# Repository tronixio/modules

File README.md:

# Modules

## GPIO Modules.

- [Breadboard.](https://github.com/tronixio/modules/blob/main/gpio/hc595.md)
- [TODO - 74HC595 - LED & Header.](https://github.com/tronixio/modules/blob/main/gpio/hc595.md)
- [TODO - 74HC4053 - Header.](https://github.com/tronixio/modules/blob/main/gpio/hc4053.md)
- [TODO - DG509B - Header.](https://github.com/tronixio/modules/blob/main/gpio/dg509b.md)
- [TODO - LCD 4x20 Characters.](https://github.com/tronixio/modules/blob/main/gpio/lcd420.md)

## UART Modules.

- [TODO.](https://tronix.io)

## I2C Modules.

- [TODO.](https://tronix.io)

## SPI Modules.

- [TODO.](https://tronix.io)

## Notes.

- DRAFT : Prototype OK, last check schematic, PCB & code can be modify.
- TODO : Work in progress, prototype was not good, hardware, PCB and code can be rework.

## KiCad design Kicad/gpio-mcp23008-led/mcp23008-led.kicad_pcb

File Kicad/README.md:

# Modules.

- [Modules.](https://github.com/tronixio/modules)

## Notes.

- TODO : Work in progress, prototype was not good, hardware, PCB and code can be rework.
- DRAFT : Prototype OK, last check schematic, PCB & code can be modify.

## DISCLAIMER.

THIS CODE IS PROVIDED WITHOUT ANY WARRANTY OR GUARANTEES.
USERS MAY USE THIS CODE FOR DEVELOPMENT AND EXAMPLE PURPOSES ONLY.
AUTHORS ARE NOT RESPONSIBLE FOR ANY ERRORS, OMISSIONS, OR DAMAGES THAT COULD
RESULT FROM USING THIS FIRMWARE IN WHOLE OR IN PART.

---

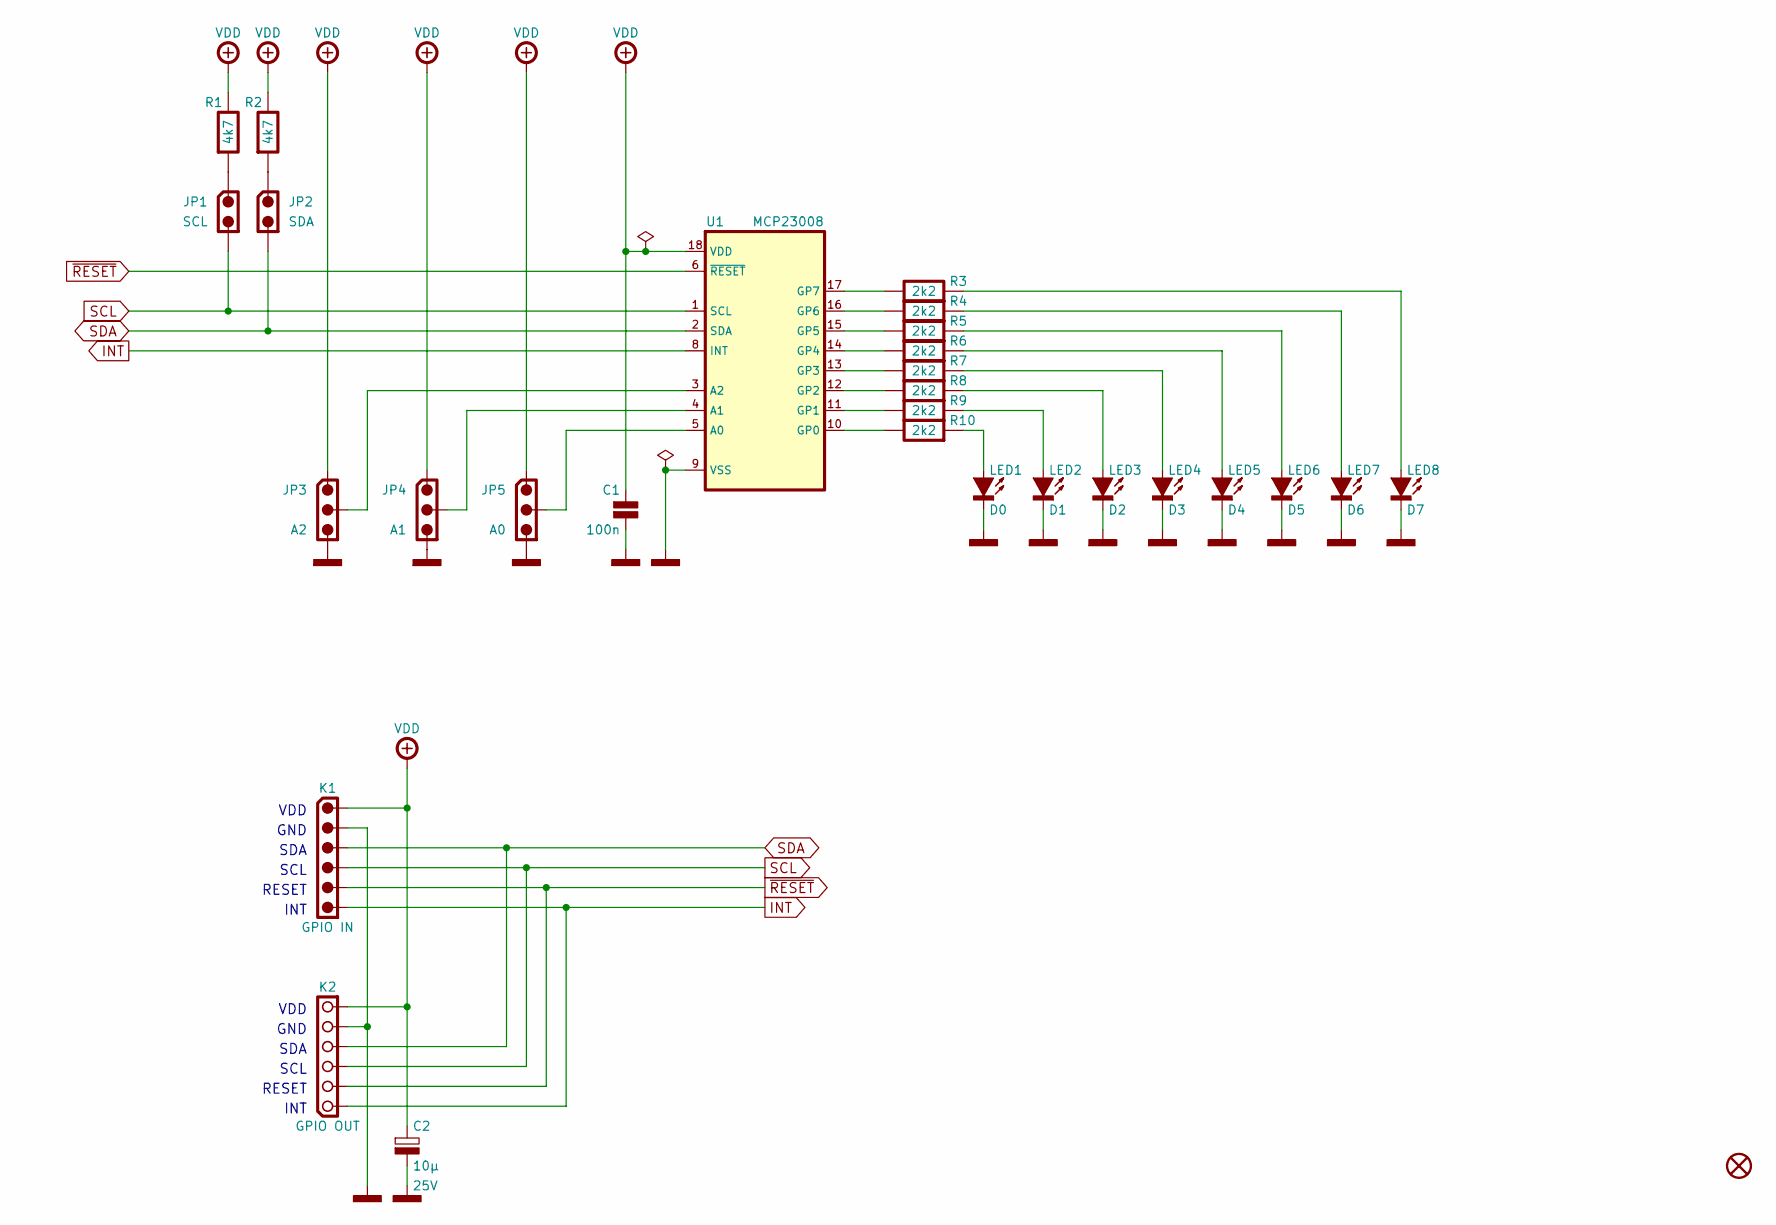
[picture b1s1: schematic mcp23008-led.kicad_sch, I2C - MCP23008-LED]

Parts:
C1: 100n; CAPACITOR-SMD-1206; Voltage 50V; Tolerance 5%; Mouser 80-C1206C104J5R
C2: 10µ; CAPACITOR-SMD-CASE-B; Voltage 25V; Tolerance 10%; Mouser 74-293D106X9025B2TE3
JP1: SCL; HARWIN-M22-25102xx; Mouser 855-M22-25102
JP2: SDA; HARWIN-M22-25102xx; Mouser 855-M22-25102
JP3: A2; HARWIN-M22-25103xx; Mouser 855-M22-25103
JP4: A1; HARWIN-M22-25103xx; Mouser 855-M22-25103
JP5: A0; HARWIN-M22-25103xx; Mouser 855-M22-25103
K1: GPIO IN; HARWIN-M20-975064x; Mouser 855-M20-975064
K2: GPIO OUT; SAMTEC-SSW-106-02-T-S-RA; Mouser 200-SSW10603TSRA
LED1: D0; LED-SMD-1206; Mouser 604-APT3216LSECKJ3RV
LED2: D1; LED-SMD-1206; Mouser 604-APT3216LSECKJ3RV
LED3: D2; LED-SMD-1206; Mouser 604-APT3216LSECKJ3RV
LED4: D3; LED-SMD-1206; Mouser 604-APT3216LSECKJ3RV
LED5: D4; LED-SMD-1206; Mouser 604-APT3216LSECKJ3RV
LED6: D5; LED-SMD-1206; Mouser 604-APT3216LSECKJ3RV
LED7: D6; LED-SMD-1206; Mouser 604-APT3216LSECKJ3RV
LED8: D7; LED-SMD-1206; Mouser 604-APT3216LSECKJ3RV
R1, R2: 4k7; RESISTOR-SMD-0805; Tolerance 5%; Mouser 660-RK73B2ATTDD472J
R3, R4, R5, R6, R7, R8, R9, R10: 2k2; RESISTOR-SMD-1206; Tolerance 5%; Mouser 660-RK73B2BTTDD222J
U1: MCP23008; SOIC-18W; Mouser 579-MCP23008-E/SO
U2: 3M-SJ5376; Mouser 517-SJ5376

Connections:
+VDD: C1.1, C2.1, JP3.1, JP4.1, JP5.1, K1.1, K2.6, R1.1, R2.1, U1.18 (VDD)
GND: C1.2, C2.2, JP3.3, JP4.3, JP5.3, K1.2, K2.5, LED1.1 (C), LED2.1 (C), LED3.1 (C), LED4.1 (C), LED5.1 (C), LED6.1 (C), LED7.1 (C), LED8.1 (C), U1.9 (VSS)
INT: K1.6, K2.1, U1.8 (INT)
unnamed: JP1.1, R1.2
unnamed: JP2.1, R2.2
unnamed: LED1.2 (A), R10.2
unnamed: LED2.2 (A), R9.2
unnamed: LED3.2 (A), R8.2
unnamed: LED4.2 (A), R7.2
unnamed: LED5.2 (A), R6.2
unnamed: LED6.2 (A), R5.2
unnamed: LED7.2 (A), R4.2
unnamed: LED8.2 (A), R3.2
unnamed: JP5.2, U1.5 (A0)
unnamed: JP4.2, U1.4 (A1)
unnamed: JP3.2, U1.3 (A2)
unnamed: R10.1, U1.10 (GP0)
unnamed: R9.1, U1.11 (GP1)
unnamed: R8.1, U1.12 (GP2)
unnamed: R7.1, U1.13 (GP3)
unnamed: R6.1, U1.14 (GP4)
unnamed: R5.1, U1.15 (GP5)
unnamed: R4.1, U1.16 (GP6)
unnamed: R3.1, U1.17 (GP7)
SCL: JP1.2, K1.4, K2.3, U1.1 (SCL)
SDA: JP2.2, K1.3, K2.4, U1.2 (SDA)
~RESET: K1.5, K2.2, U1.6 (~RESET)

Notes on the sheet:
SCL
RESET
INT
GND
VDD
SDA

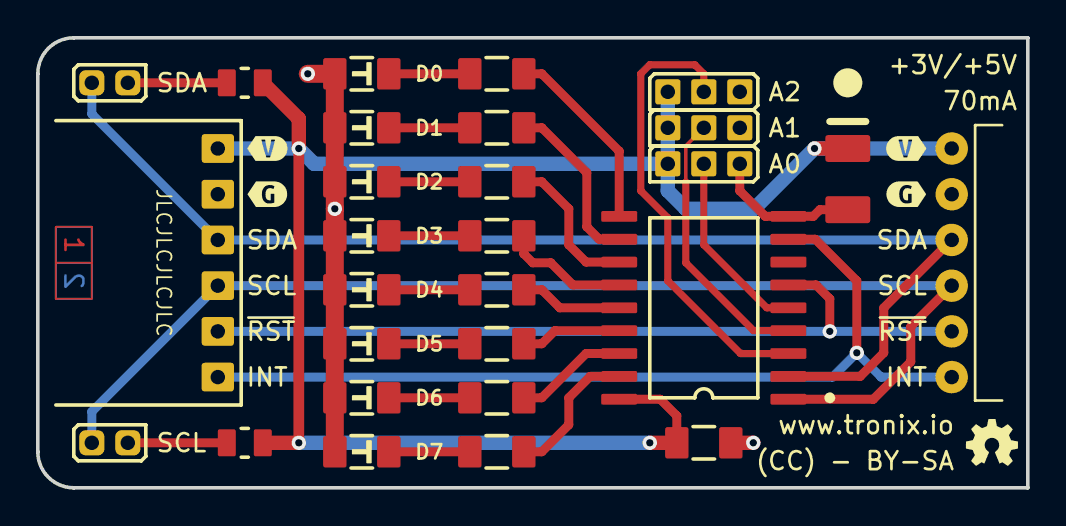
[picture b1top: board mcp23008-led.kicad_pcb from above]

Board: 2 copper layers, 55.0 x 25.0 mm, 33 parts (1 on the bottom side), 27 nets.

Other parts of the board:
kibuzzard-62B79DF9: G***; kibuzzard-62B79DF9
kibuzzard-62B79E59: G***; kibuzzard-62B79E59
kibuzzard-62B79EB2: G***; kibuzzard-62B79EB2
kibuzzard-62B79EC3: G***; kibuzzard-62B79EC3

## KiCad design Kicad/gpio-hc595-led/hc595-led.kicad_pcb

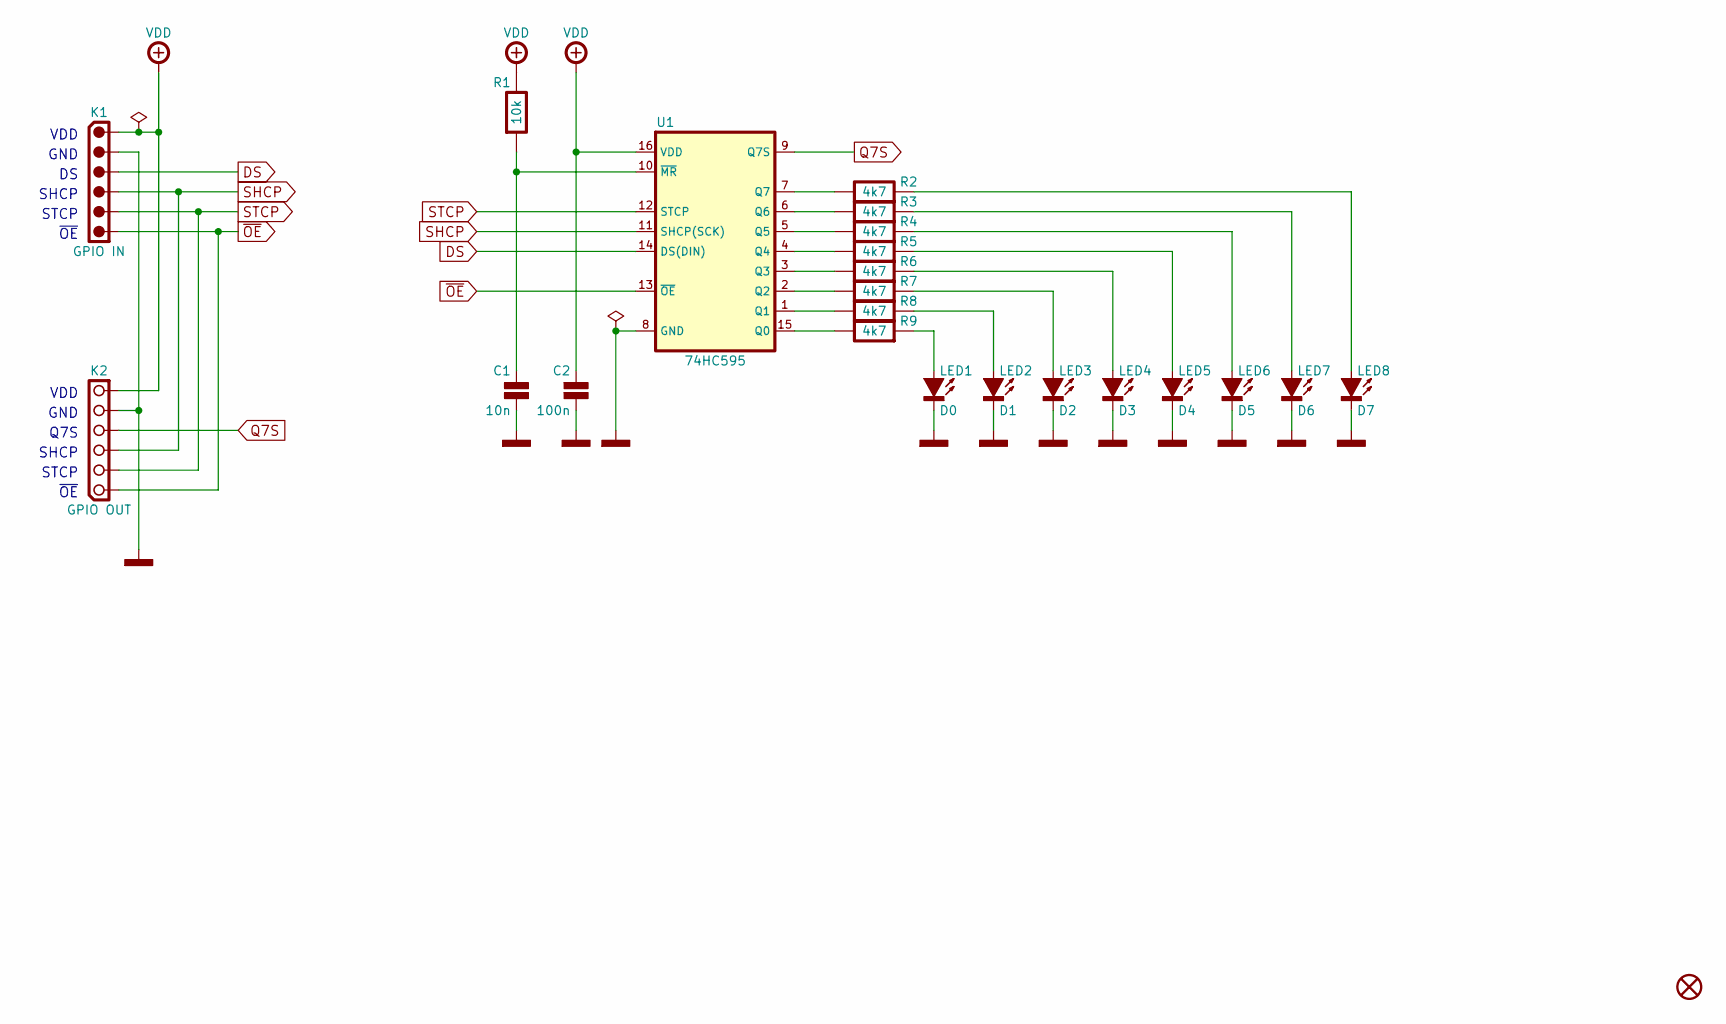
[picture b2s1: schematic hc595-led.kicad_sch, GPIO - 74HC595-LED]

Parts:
C1: 10n; CAPACITOR-SMD-1206; Voltage 50V; Tolerance 5%; Mouser 80-C1206C103J5R
C2: 100n; CAPACITOR-SMD-1206; Voltage 50V; Tolerance 5%; Mouser 80-C1206C104J5R
K1: GPIO IN; HARWIN-M20-975064x; Mouser 855-M20-975064
K2: GPIO OUT; SAMTEC-SSW-106-02-T-S-RA; Mouser 200-SSW10603TSRA
LED1: D0; LED-SMD-1206; Mouser 604-APT3216LSECKJ3RV
LED2: D1; LED-SMD-1206; Mouser 604-APT3216LSECKJ3RV
LED3: D2; LED-SMD-1206; Mouser 604-APT3216LSECKJ3RV
LED4: D3; LED-SMD-1206; Mouser 604-APT3216LSECKJ3RV
LED5: D4; LED-SMD-1206; Mouser 604-APT3216LSECKJ3RV
LED6: D5; LED-SMD-1206; Mouser 604-APT3216LSECKJ3RV
LED7: D6; LED-SMD-1206; Mouser 604-APT3216LSECKJ3RV
LED8: D7; LED-SMD-1206; Mouser 604-APT3216LSECKJ3RV
R1: 10k; RESISTOR-SMD-1206; Tolerance 5%; Mouser 660-RK73B2BTTDD103J
R2, R3, R4, R5, R6, R7, R8, R9: 4k7; RESISTOR-SMD-1206; Tolerance 5%; Mouser 660-RK73B2BTTDD472J
U1: 74HC595; SOIC-16; Mouser 771-AHC595D
U2: 3M-SJ5376; Mouser 517-SJ5376

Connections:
+VDD: C2.1, K1.1, K2.6, R1.1, U1.16 (VDD)
DS: K1.3, U1.14 (DS(DIN))
GND: C1.2, C2.2, K1.2, K2.5, LED1.1 (C), LED2.1 (C), LED3.1 (C), LED4.1 (C), LED5.1 (C), LED6.1 (C), LED7.1 (C), LED8.1 (C), U1.8 (GND)
unnamed: LED1.2 (A), R9.2
unnamed: LED2.2 (A), R8.2
unnamed: LED3.2 (A), R7.2
unnamed: LED4.2 (A), R6.2
unnamed: LED5.2 (A), R5.2
unnamed: LED6.2 (A), R4.2
unnamed: LED7.2 (A), R3.2
unnamed: LED8.2 (A), R2.2
unnamed: R9.1, U1.15 (Q0)
unnamed: R8.1, U1.1 (Q1)
unnamed: R7.1, U1.2 (Q2)
unnamed: R6.1, U1.3 (Q3)
unnamed: R5.1, U1.4 (Q4)
unnamed: R4.1, U1.5 (Q5)
unnamed: R3.1, U1.6 (Q6)
unnamed: R2.1, U1.7 (Q7)
unnamed: C1.1, R1.2, U1.10 (~MR)
Q7S: K2.4, U1.9 (Q7S)
SHCP: K1.4, K2.3, U1.11 (SHCP(SCK))
STCP: K1.5, K2.2, U1.12 (STCP)
~OE: K1.6, K2.1, U1.13 (~OE)

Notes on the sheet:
SHCP
STCP
~{OE}
GND
VDD
Q7S

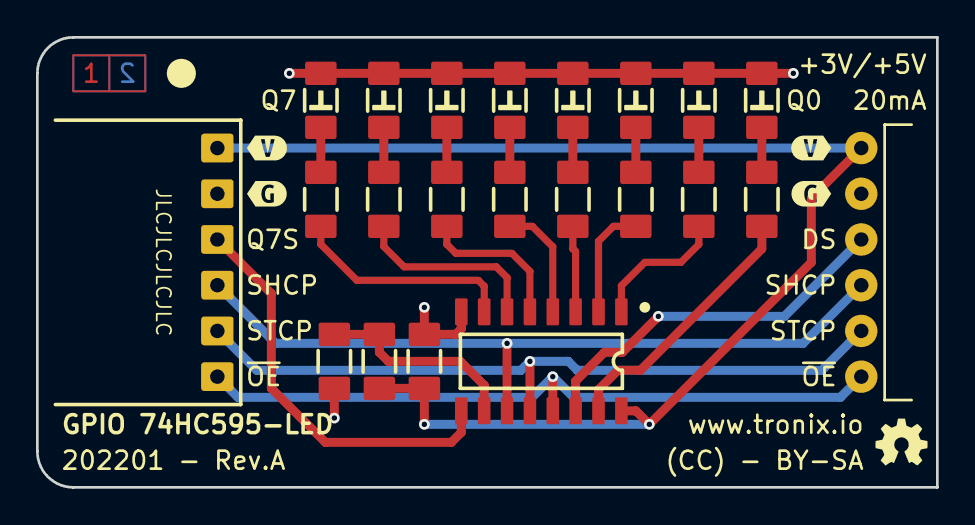
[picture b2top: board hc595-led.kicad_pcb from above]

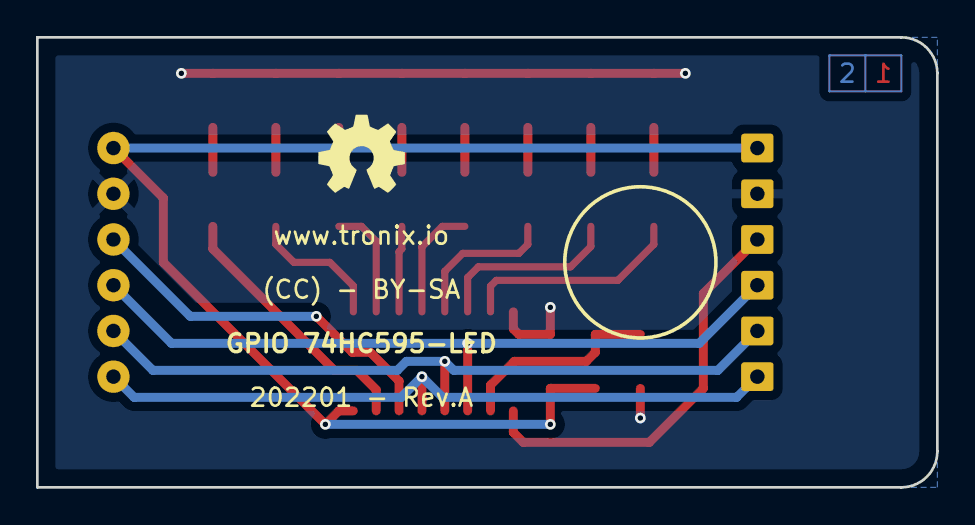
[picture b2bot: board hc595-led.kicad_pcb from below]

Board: 2 copper layers, 50.0 x 25.0 mm, 28 parts (2 on the bottom side), 24 nets.

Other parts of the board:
GT: LOGO; OSHW-5MM
kibuzzard-62B79DF9: G***; kibuzzard-62B79DF9
kibuzzard-62B79E59: G***; kibuzzard-62B79E59
kibuzzard-62B79EB2: G***; kibuzzard-62B79EB2
kibuzzard-62B79EC3: G***; kibuzzard-62B79EC3

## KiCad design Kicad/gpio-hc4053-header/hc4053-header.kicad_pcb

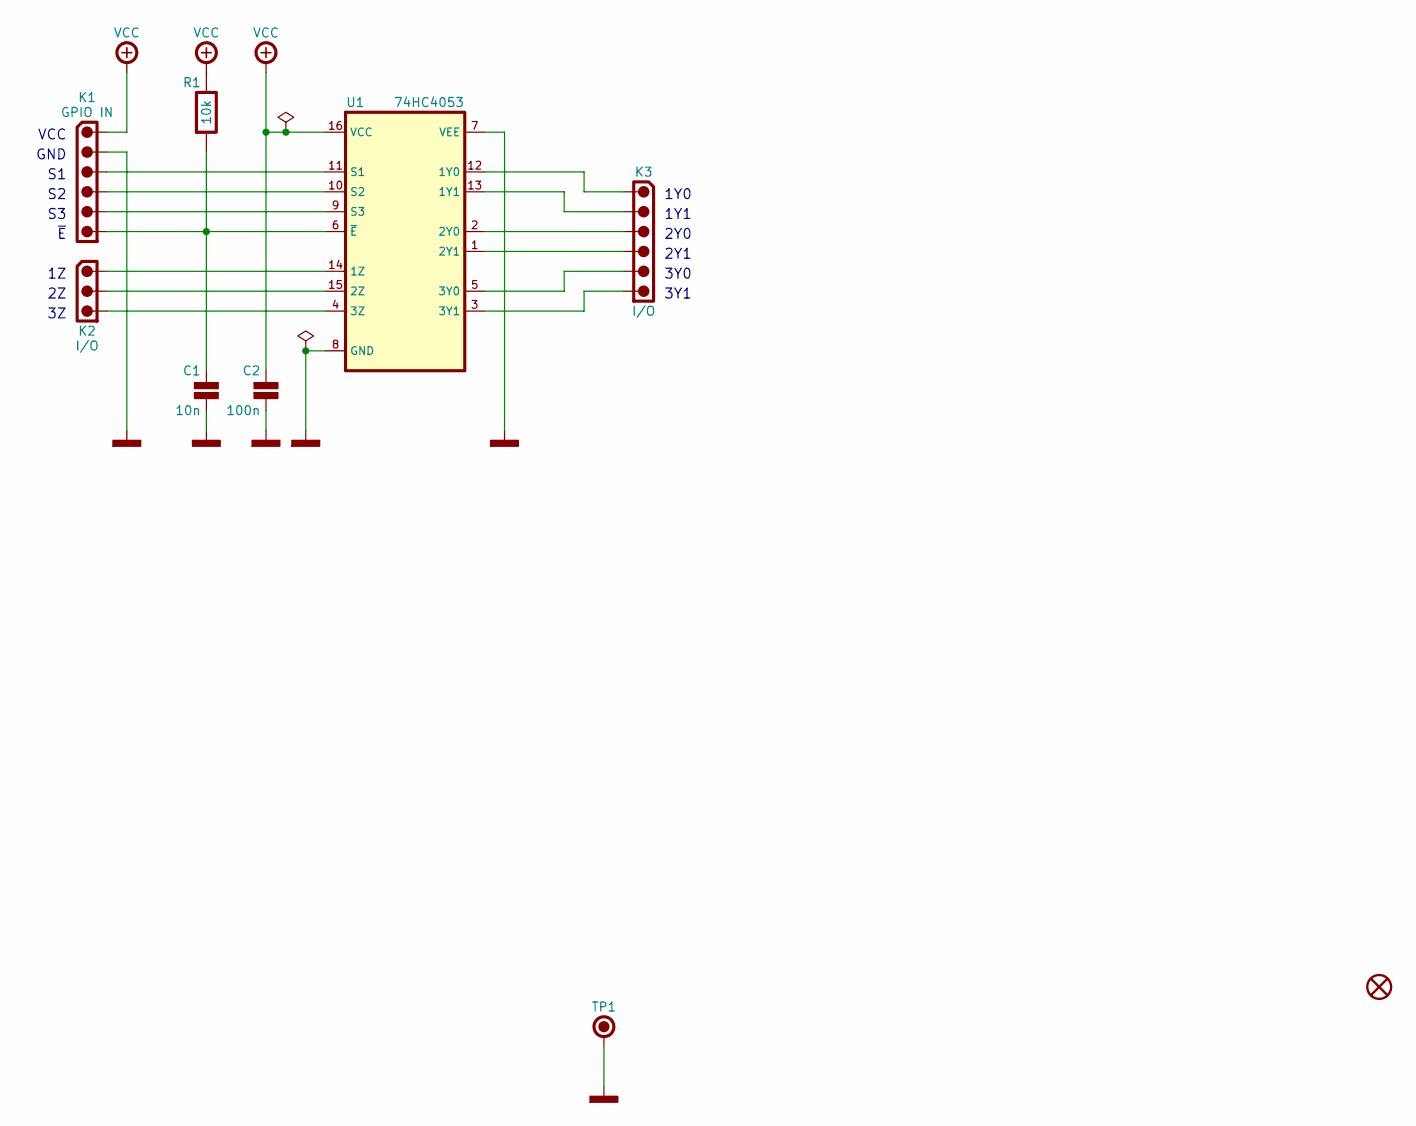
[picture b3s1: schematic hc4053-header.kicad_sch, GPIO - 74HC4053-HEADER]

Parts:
C1: 10n; CAPACITOR-SMD-1206; Voltage 50V; Tolerance 5%; Mouser 80-C1206C104J5R
C2: 100n; CAPACITOR-SMD-1206; Voltage 50V; Tolerance 5%; Mouser 80-C1206C104J5R
K1: GPIO IN; HARWIN-M20-975064x; Mouser 855-M20-975064
K2: I/O; HARWIN-M20-999034x; Mouser 855-M20-999034
K3: I/O; HARWIN-M20-999064x; Mouser 855-M20-999064
R1: 10k; RESISTOR-SMD-1206; Tolerance 5%; Mouser 660-RK73B2BTTDD103J
TP1: GND; KEYSTONE-2000-3; Mouser 534-2000-3
U1: 74HC4053; SOIC-16; Mouser 771-74HC4053D
U2: 3M-SJ5376; Mouser 517-SJ5376

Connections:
+VCC: C2.1, K1.1, R1.1, U1.16 (VCC)
GND: C1.2, C2.2, K1.2, TP1.1, U1.7 (VEE), U1.8 (GND)
unnamed: K3.1, U1.12 (1Y0)
unnamed: K3.2, U1.13 (1Y1)
unnamed: K2.1, U1.14 (1Z)
unnamed: K3.3, U1.2 (2Y0)
unnamed: K3.4, U1.1 (2Y1)
unnamed: K2.2, U1.15 (2Z)
unnamed: K3.5, U1.5 (3Y0)
unnamed: K3.6, U1.3 (3Y1)
unnamed: K2.3, U1.4 (3Z)
unnamed: K1.3, U1.11 (S1)
unnamed: K1.4, U1.10 (S2)
unnamed: K1.5, U1.9 (S3)
unnamed: C1.1, K1.6, R1.2, U1.6 (~E)

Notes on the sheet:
2Y1
1Y1
~{E}
VCC
3Y0
3Y1
2Y0
GND
1Y0

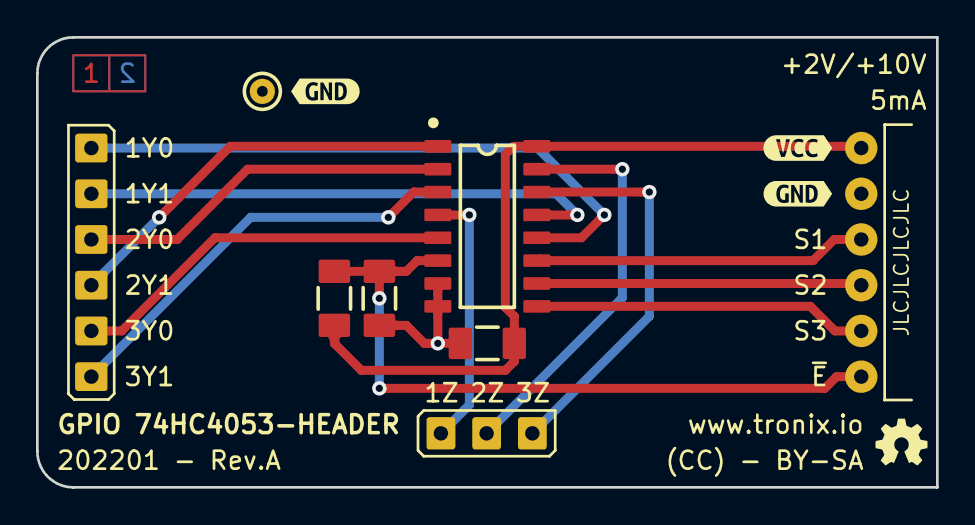
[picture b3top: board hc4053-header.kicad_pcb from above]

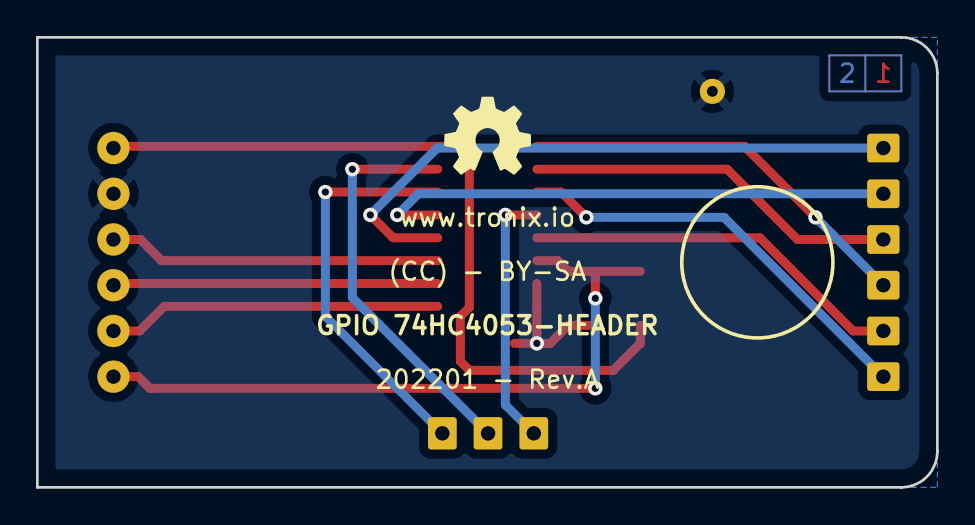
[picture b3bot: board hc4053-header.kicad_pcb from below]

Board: 2 copper layers, 50.0 x 25.0 mm, 13 parts (2 on the bottom side), 15 nets.

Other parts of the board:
GT: LOGO; OSHW-5MM
kibuzzard-62B2FE3C: G***; kibuzzard-62B2FE3C
kibuzzard-62B2FE4D: G***; kibuzzard-62B2FE4D
kibuzzard-63494430: G***; kibuzzard-63494430

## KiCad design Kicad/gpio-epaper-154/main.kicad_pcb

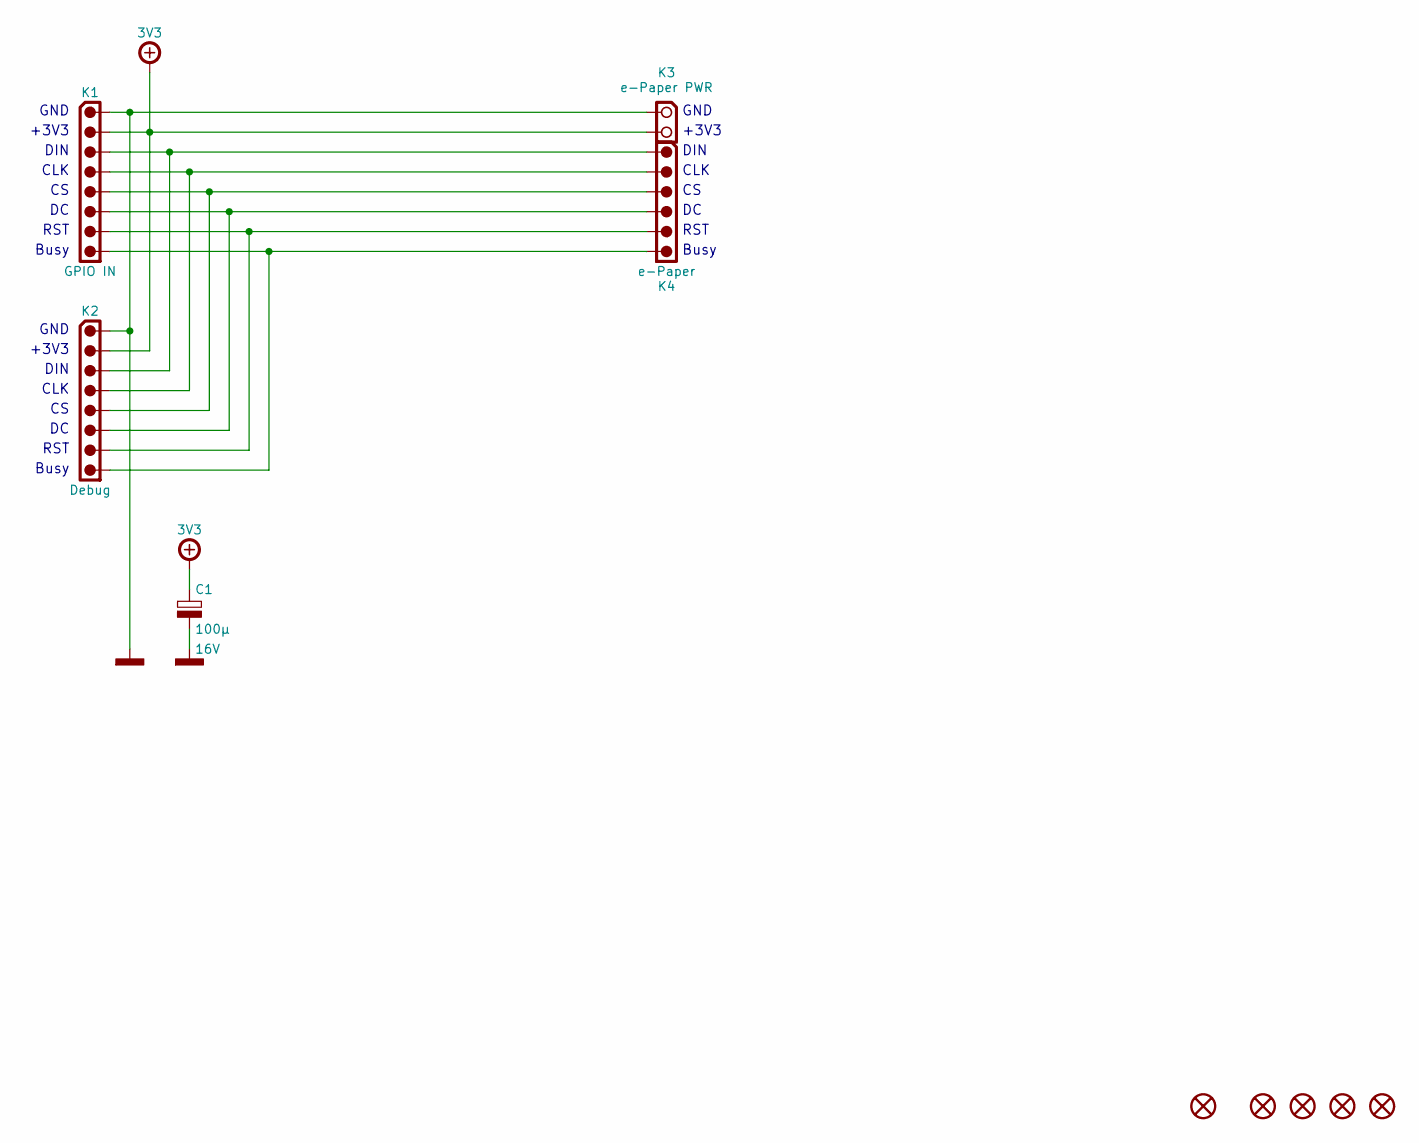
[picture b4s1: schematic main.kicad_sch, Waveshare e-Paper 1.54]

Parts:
C1: 100µ; CAPACITOR-ELECTROLYTIC-RADIAL-050-110-020-WURTH; Tolerance 20%; Voltage 16V; Mouser 710-860020372006
H1, H2, H3, H4: MOUNTING-HOLE-3MM; MOUNTING-HOLE-3MM-MASK
K1: GPIO IN; HARWIN-M20-999084x; Mouser 855-M20-999084
K2: Debug; HARWIN-M20-999084x; Mouser 855-M20-999084
K3: e-Paper PWR; HARWIN-M20-782024x; Mouser 855-M20-782024
K4: e-Paper; HARWIN-M20-999064x; Mouser 855-M20-999064
LCD1: e-Paper 1.54; WAVESHARE-EPAPER-154

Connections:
+3V3: C1.1, K1.2, K2.2, K3.2
GND: C1.2, K1.1, K2.1, K3.1
unnamed: K1.3, K2.3, K4.1
unnamed: K1.4, K2.4, K4.2
unnamed: K1.5, K2.5, K4.3
unnamed: K1.6, K2.6, K4.4
unnamed: K1.7, K2.7, K4.5
unnamed: K1.8, K2.8, K4.6

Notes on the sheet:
+3V3
CLK
RST
Busy
DIN
GND

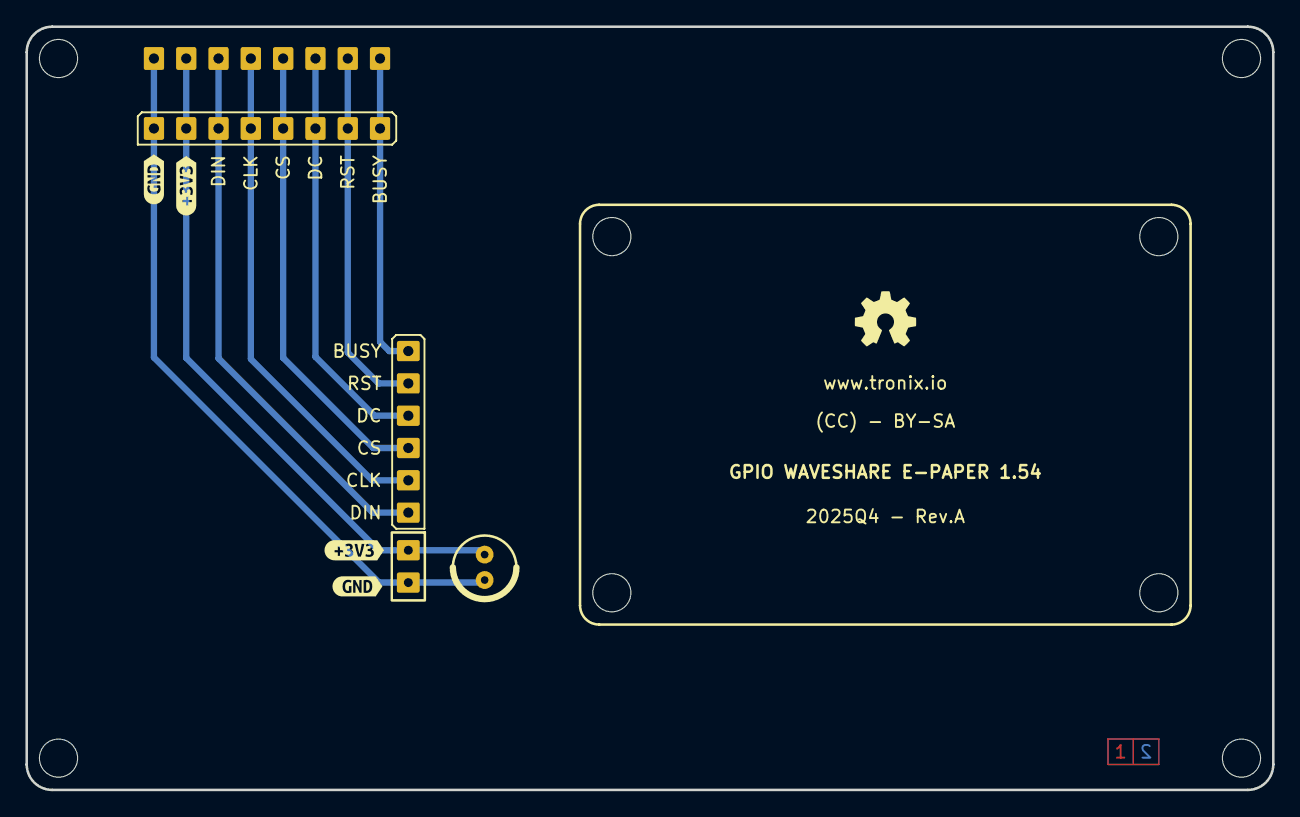
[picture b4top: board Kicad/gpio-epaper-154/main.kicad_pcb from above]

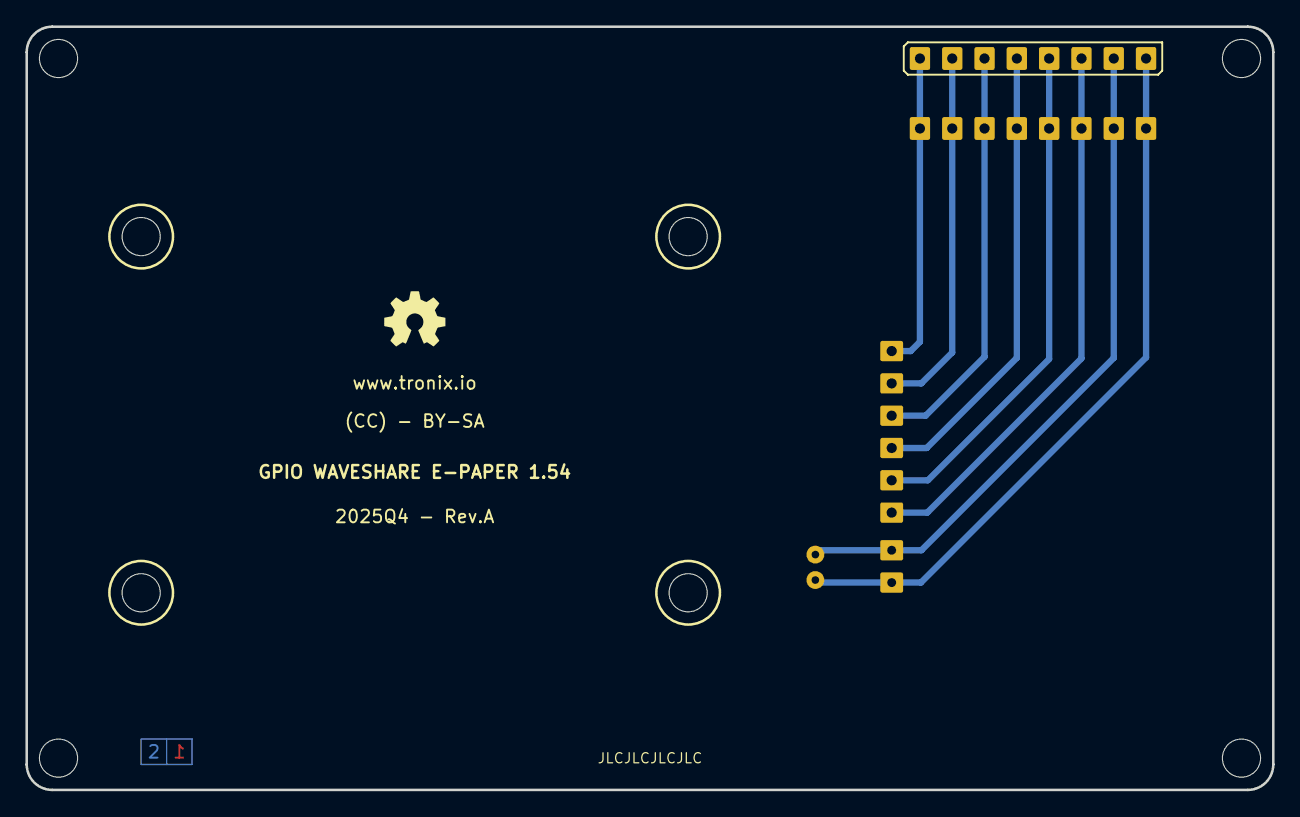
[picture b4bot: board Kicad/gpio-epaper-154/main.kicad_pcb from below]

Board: 2 copper layers, 98.0 x 60.0 mm, 16 parts (2 on the bottom side), 8 nets.

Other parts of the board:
GT: LOGO; OSHW-5MM
GT#2: LOGO; OSHW-5MM
kibuzzard-68CDAEAB, kibuzzard-68CDAEAB#2: G***; kibuzzard-68CDAEAB
kibuzzard-68CDAEC0, kibuzzard-68CDAEC0#2: G***; kibuzzard-68CDAEC0

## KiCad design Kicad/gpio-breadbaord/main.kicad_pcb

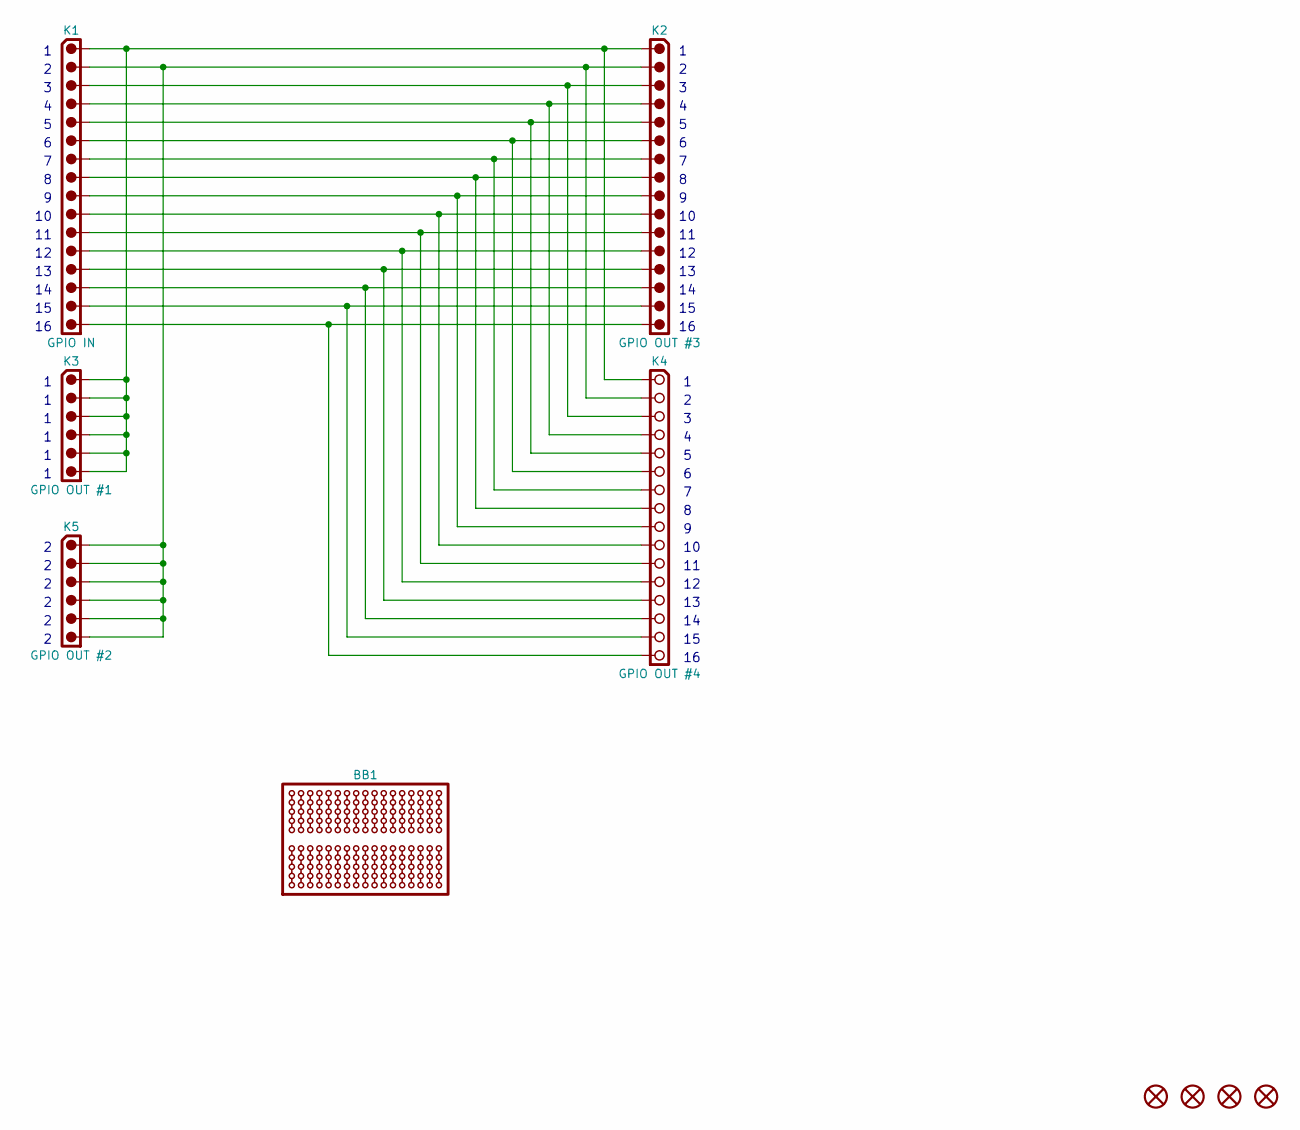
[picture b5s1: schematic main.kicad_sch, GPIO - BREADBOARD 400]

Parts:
BB1: BREADBOARD-400; Mouser 854-BB400
H1, H2, H3, H4: MOUNTING-HOLE-3MM; MOUNTING-HOLE-3MM-MASK
K1: GPIO IN; HARWIN-M20-999164x; Mouser 855-M20-999164
K2: GPIO OUT #3; HARWIN-M20-999164x; Mouser 855-M20-999164
K3: GPIO OUT #1; HARWIN-M20-999064x; Mouser 855-M20-999064
K4: GPIO OUT #4; HARWIN-M20-782164x; Mouser 855-M20-782164
K5: GPIO OUT #2; HARWIN-M20-999064x; Mouser 855-M20-999064

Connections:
unnamed: K1.1, K2.1, K3.1, K3.2, K3.3, K3.4, K3.5, K3.6, K4.1
unnamed: K1.2, K2.2, K4.2, K5.1, K5.2, K5.3, K5.4, K5.5, K5.6
unnamed: K1.3, K2.3, K4.3
unnamed: K1.4, K2.4, K4.4
unnamed: K1.5, K2.5, K4.5
unnamed: K1.6, K2.6, K4.6
unnamed: K1.7, K2.7, K4.7
unnamed: K1.8, K2.8, K4.8
unnamed: K1.9, K2.9, K4.9
unnamed: K1.10, K2.10, K4.10
unnamed: K1.11, K2.11, K4.11
unnamed: K1.12, K2.12, K4.12
unnamed: K1.13, K2.13, K4.13
unnamed: K1.14, K2.14, K4.14
unnamed: K1.15, K2.15, K4.15
unnamed: K1.16, K2.16, K4.16

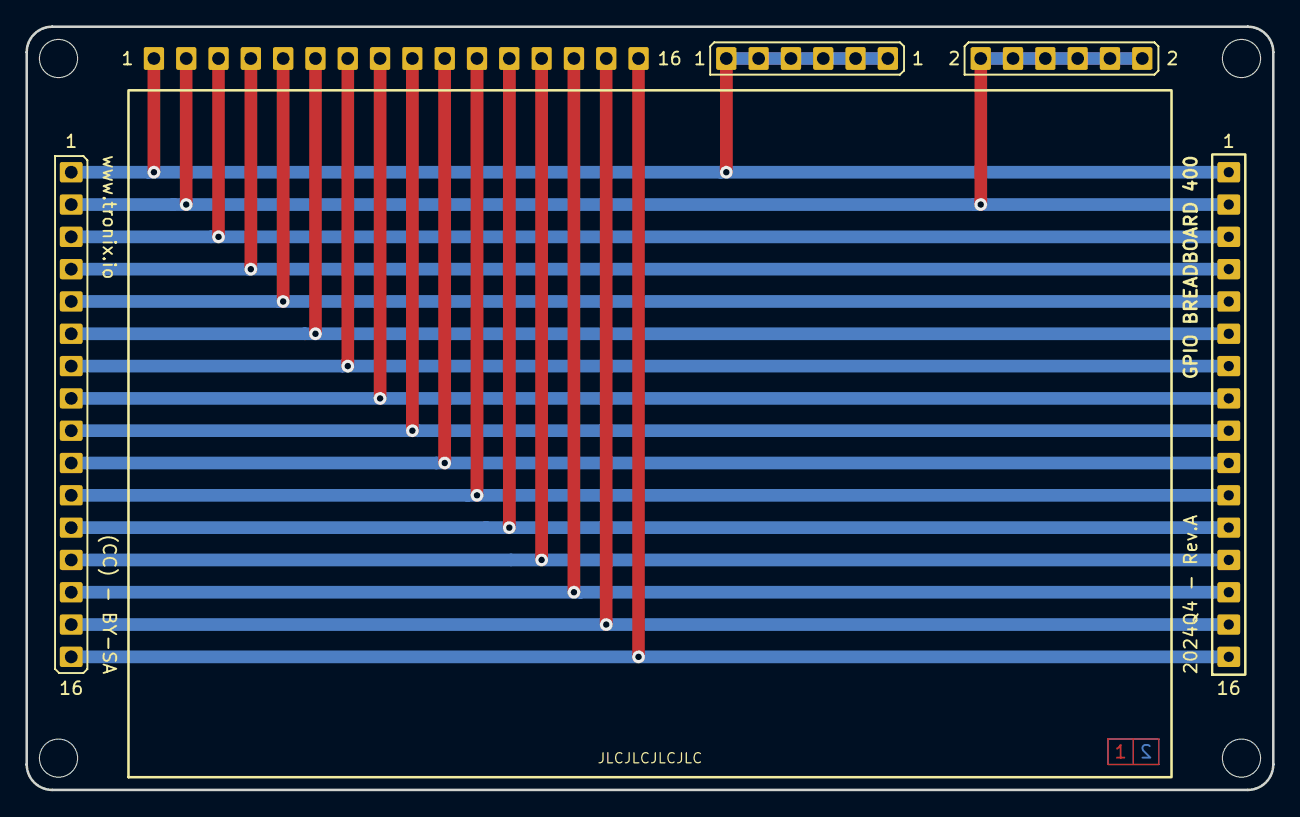
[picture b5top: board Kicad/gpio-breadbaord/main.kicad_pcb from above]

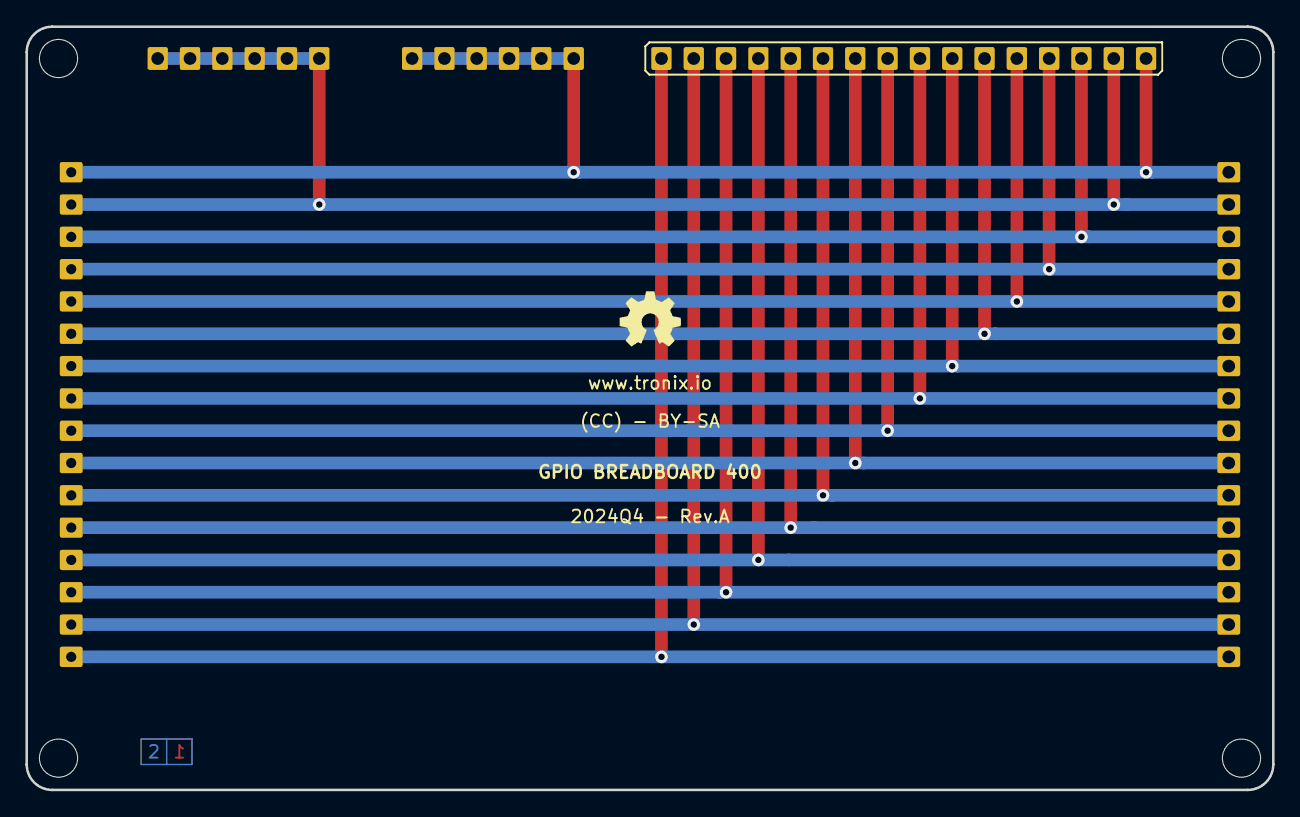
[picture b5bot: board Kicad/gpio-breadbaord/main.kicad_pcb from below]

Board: 2 copper layers, 98.0 x 60.0 mm, 11 parts (2 on the bottom side), 16 nets.

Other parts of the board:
GT: LOGO; OSHW-5MM
